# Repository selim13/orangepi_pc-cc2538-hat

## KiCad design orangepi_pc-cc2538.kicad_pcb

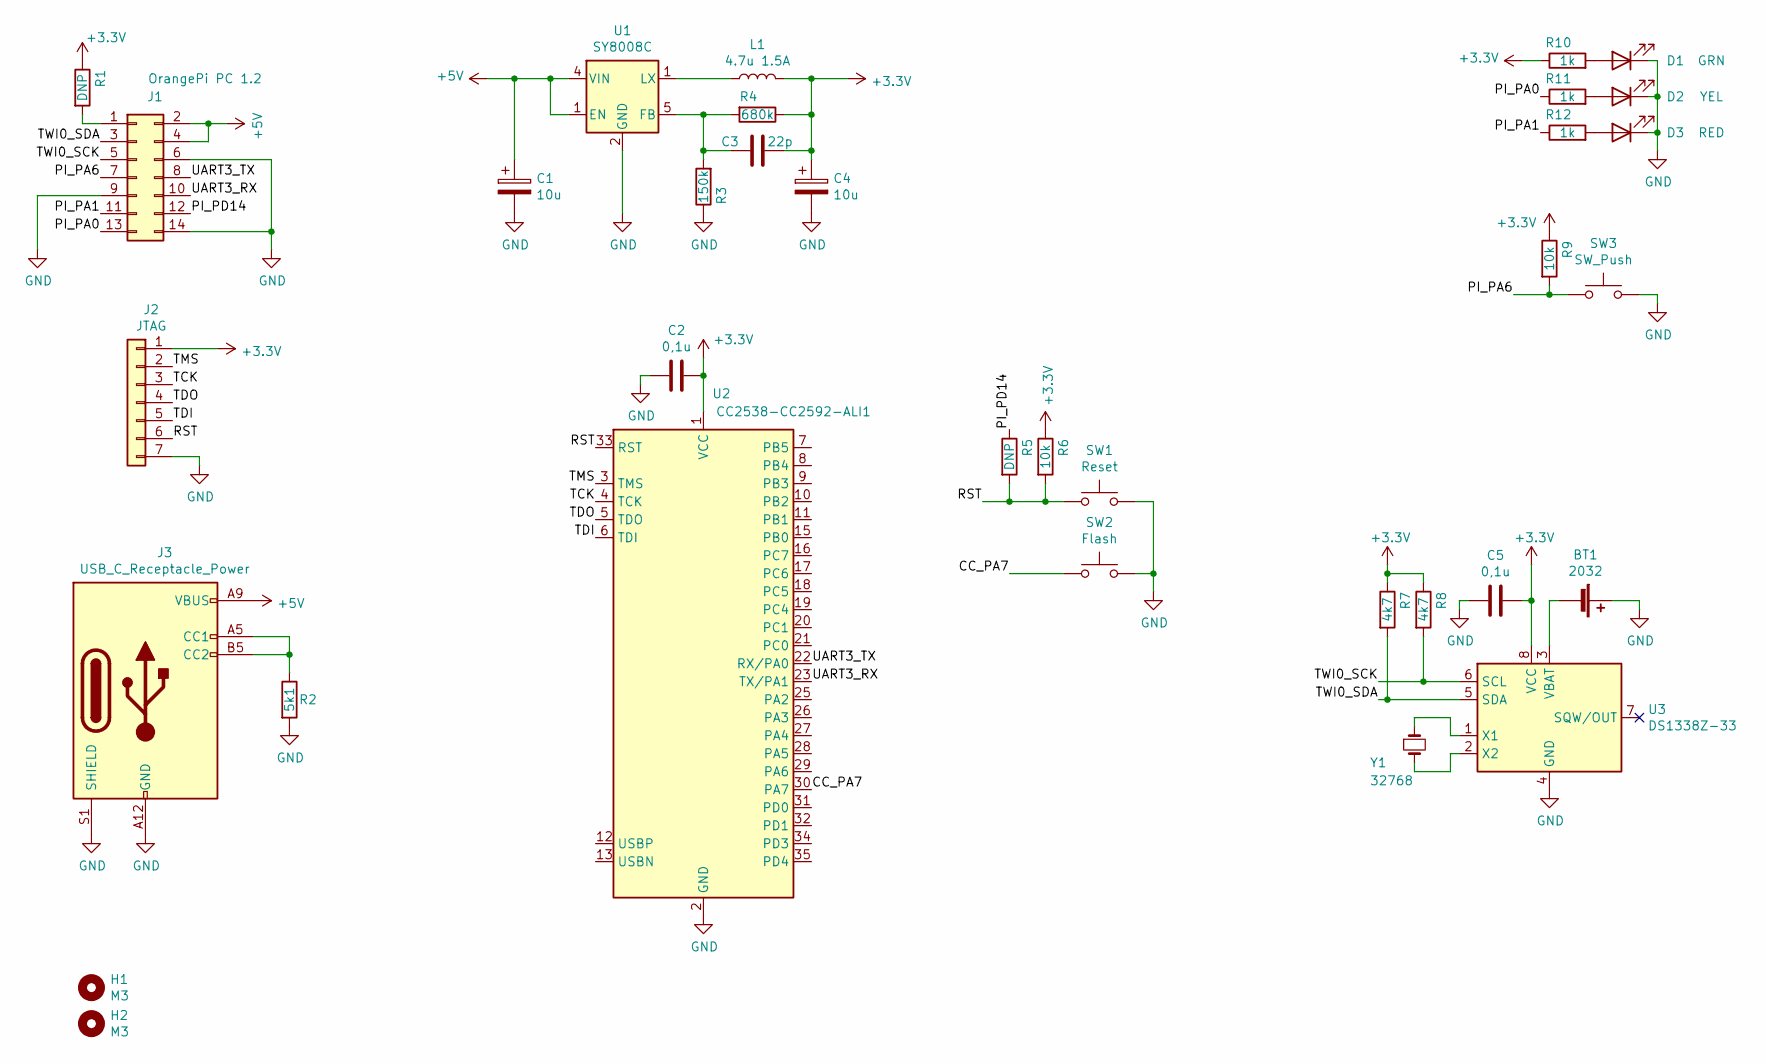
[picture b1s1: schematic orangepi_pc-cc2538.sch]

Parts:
BT1: 2032; BatteryHolder_Keystone_3002_1x2032
C1, C4: 10u; CP_EIA-3216-18_Kemet-A
C2, C5: 0,1u; C_0603_1608Metric
C3: 22p; C_0603_1608Metric
D1: GRN; LED_0805_2012Metric
D2: YEL; LED_0805_2012Metric
D3: RED; LED_0805_2012Metric
H1, H2: M3; MountingHole_3.2mm_M3
J1: OrangePi PC 1.2; PinSocket_2x07_P2.54mm_Vertical
J2: JTAG; PinHeader_1x07_P2.54mm_Vertical
J3: USB_C_Receptacle_Power; USB_C_Receptacle_HRO_TYPE-C-31-M-12
L1: 4.7u 1.5A; L_6.3x6.3_H3
R1, R5: DNP; R_0603_1608Metric
R2: 5k1; R_0603_1608Metric
R3: 150k; R_0603_1608Metric
R4: 680k; R_0603_1608Metric
R6, R9: 10k; R_0603_1608Metric
R7, R8: 4k7; R_0603_1608Metric
R10, R11, R12: 1k; R_0603_1608Metric
SW1: Reset; SW_SPST_B3U-1000P
SW2: Flash; SW_SPST_B3U-1000P
SW3: SW_Push; SW_Tactile_SPST_Angled_PTS645Vx39-2LFS
U1: SY8008C; SOT-23-5
U2: CC2538-CC2592-ALI1
U3: DS1338Z-33; SOIC-8_3.9x4.9mm_P1.27mm
Y1: 32768; Crystal_SMD_SeikoEpson_MC406-4Pin_9.6x4.1mm

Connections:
+3V3: C2.1, C3.2, C4.1, C5.1, J2.1, L1.2, R1.1, R4.1, R6.1, R7.1, R8.1, R9.1, R10.1, U2.1 (VCC), U3.8 (VCC)
/CC_PA7: SW2.1, U2.30 (PA7)
/PI_PA0: J1.13, R11.1
/PI_PA1: J1.11, R12.1
/PI_PA6: J1.7, R9.2, SW3.1
/PI_PD14: J1.12, R5.1
/RST: J2.6, R5.2, R6.2, SW1.1, U2.33 (RST)
/TCK: J2.3, U2.4 (TCK)
/TDI: J2.5, U2.6 (TDI)
/TDO: J2.4, U2.5 (TDO)
/TMS: J2.2, U2.3 (TMS)
/TWI0_SCK: J1.5, R8.2, U3.6 (SCL)
/TWI0_SDA: J1.3, R7.2, U3.5 (SDA)
/UART3_RX: J1.10, U2.23 (TX/PA1)
/UART3_TX: J1.8, U2.22 (RX/PA0)
GND: BT1.1 (+), C1.2, C2.2, C4.2, C5.2, D1.1 (K), D2.1 (K), D3.1 (K), J1.6, J1.9, J1.14, J2.7, J3.A12 (GND), J3.B12 (GND), J3.S1 (SHIELD), R2.2, R3.1, SW1.2, SW2.2, SW3.2, U1.2 (GND), U2.2 (GND), U2.15 (14), U2.24 (GND), U2.36 (GND), U3.4 (GND)
unnamed: BT1.2 (-), U3.3 (VBAT)
unnamed: C3.1, R3.2, R4.2, U1.5 (FB)
unnamed: D1.2 (A), R10.2
unnamed: D2.2 (A), R11.2
unnamed: D3.2 (A), R12.2
unnamed: J1.1, R1.2
unnamed: J3.A5 (CC1), J3.B5 (CC2), R2.1
unnamed: U3.1 (X1), Y1.1
unnamed: U3.2 (X2), Y1.2

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
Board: 2 copper layers, 33 parts (1 on the bottom side), 19 nets, no tracks yet.

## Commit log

2020-07-26 add RTC, LEDs, buttons to schematic
2020-08-01 add board outline
